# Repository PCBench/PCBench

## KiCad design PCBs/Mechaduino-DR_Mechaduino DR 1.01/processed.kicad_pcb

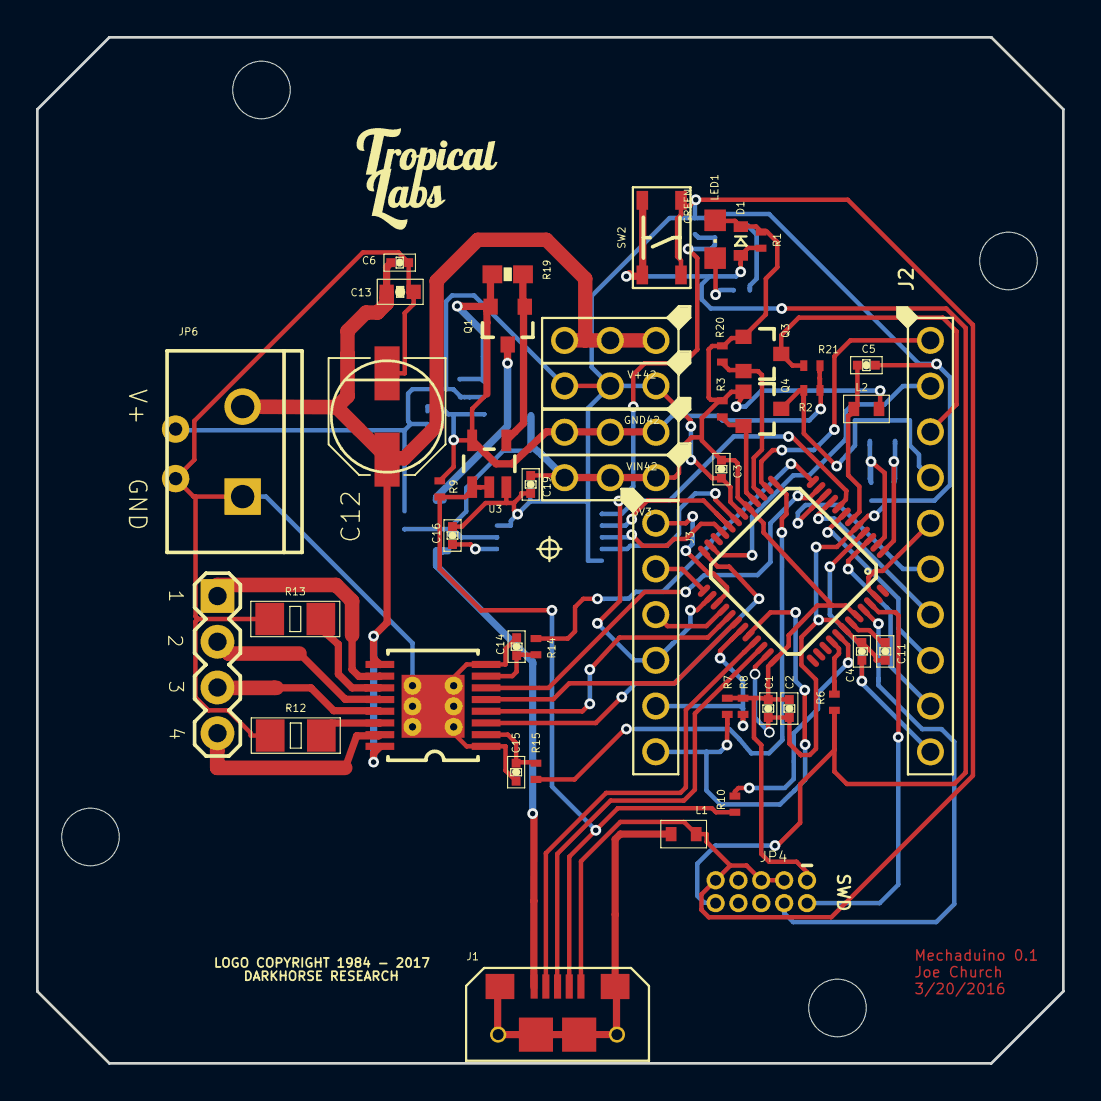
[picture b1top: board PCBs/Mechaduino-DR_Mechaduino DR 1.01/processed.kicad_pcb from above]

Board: 2 copper layers, 57.0 x 57.0 mm, 68 parts (0 on the bottom side), 60 nets.

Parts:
3V3: HEADER_01X03_2.54MM
C1, C2, C3, C4, C5, C9, C14, C15, C16, C19: 0.1uF; SWIFT_0402-CAP
C6: 0.01uF; 0402-CAP
C7, C8: 22pF; SWIFT_0402-CAP
C10: 10uF; 0805-CAP
C11, C17: 1uF; SWIFT_0402-CAP
C12: 100uF; CAPACITORS_ELECTROL_6.6X6.6
C13: 1.0uF; 0603-CAP
C18: 10.0uF; C0805
D1: DIODE_SOD-123
F1: 500mA; FUSE_SMD-PTC-1206
FRAME1: FRAME-LEDGER; CREATIVE_COMMONS
GND42: HEADER_01X03_2.54MM
HS: HS; Heat_Sink
IC1: SAMD21G18A-AUT; TQFP48-7X7
J1: USB_MICRO_RIGHT; USB_MICRO-RIGHT
J2: HEADER_01X10_2.54MM; PTH_2.54MM_01X10
J3: HEADER_01X06_2.54MM
JP4: SWD; CONNECTOR_PINHEAD-2X5-P127
JP6: CONNECTORS_M04PTH
L1: INDUCTOR_0603-TDK
L2: BLM18PG471SN1D; 0603-TDK
LED1: GREEN; CHIPLED_0805
MOTOR_POWER42: SCREWTERMINAL-5MM-2
MOT_GRAPHICS_1: WANTAI_57BYGH115-003B; MOT_GRAPHICS_1
Q1: 2.5A 30V; MOSFET_P_CHANNEL_SOT23
Q2: 2N7002PW; DISCRETE_SEMI_SOT323
Q3, Q4: BSS138; MOSFET-N_CHANNEL_SOT23-3
R1, R9, R16: 100K; R0402
R2, R3, R20, R21: 10K; R0402
R5, R6, R10: 330; R0402
R7, R8: 4.7K; R0402
R12, R13: 0.15 ohm; R1206
R14, R15: 1K; R0402
R19: 47K; 0603-RES
SH1: SHORT-HA5; SHORT_ALL-50
SW2: TACT_4.2MM
U1: AS5047D_TSSOP14
U2: ALLEGRO_A4954_TSSOP16
U3: 74AHC1G125; DIGITAL_IC_SOT23-5
U4: 3.3V_REG; SOT23-5_1
U$3: TROPICAL_LABS_LOGO_1LOGO3; LOGO3
U$5: MECHADUINO_LOGO
V+42: HEADER_01X03_2.54MM
VIN42: HEADER_01X03_2.54MM
Y1: 32,768Khz; CRYSTAL-SMD-2.0X1.2

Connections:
3.3V: 3V3.P$1, 3V3.P$2, 3V3.P$3, C1.1, C2.1, C3.1, C10.1, C17.1, C19.1, D1.K, IC1.17, IC1.36, IC1.44, JP4.1, L2.1, LED1.A, Q3.1, Q4.1, R1.1, R3.1, R7.1, R8.1, R20.1, U1.12, U4.5
/ARDUINO_A0: IC1.3, J2.P$9
/ARDUINO_A1: IC1.7, J2.P$8
/ARDUINO_A2----HEADER_SS: IC1.8, U1.1
/ARDUINO_A3: IC1.9, J2.P$7
/ARDUINO_A4: IC1.10, J2.P$6
/ARDUINO_A5: IC1.47, J2.P$5
/ARDUINO_AREF: C4.1, IC1.4, J2.P$10
/ARDUINO_D0: IC1.16, Q4.2, R3.2
/ARDUINO_D1: IC1.15, Q3.2, R20.2
/ARDUINO_D2: IC1.23, J2.P$2
/ARDUINO_D3: IC1.14, J2.P$1
/ARDUINO_D4----VREF2: IC1.13, R15.2
/ARDUINO_D5----IN3: IC1.24, U2.3
/ARDUINO_D6----IN4: IC1.29, U2.4
/ARDUINO_D7----IN2: IC1.30, U2.5
/ARDUINO_D8----IN1: IC1.11, U2.6
/ARDUINO_D9----VREF1: IC1.12, R14.2
/ARDUINO_D10_SS: IC1.27, J3.P$1
/ARDUINO_D11_MOSI: IC1.25, J3.P$2
/ARDUINO_D12_MISO: IC1.28, J3.P$3
/ARDUINO_D13_SCK: IC1.26, J3.P$4, Q2.1, R16.1
/ARDUINO_D20_SDA: IC1.31, J3.P$5, R8.2
/ARDUINO_D21_SCL: IC1.32, J3.P$6, R7.2
/HEADER_MISO: IC1.21, U1.3
/HEADER_MOSI: IC1.19, U1.4
/HEADER_SCK: IC1.20, U1.2
/HV1: J2.P$3, Q3.3, R21.2
/HV2: J2.P$4, Q4.3, R2.2
/N$1: LED1.C, R5.1
/N$2: R12.2, U2.14
/N$3: Q2.3, R5.2
/N$4: R13.2, U2.11
/N$6: C15.1, R15.1, U2.2
/N$7: J1.4, R9.2, R10.1, U3.1, U3.2
/N$13: JP6.4, U2.15
/N$14: JP6.1, U2.10
/N$15: JP6.2, U2.12
/N$16: JP6.3, U2.13
/N$27: C16.1, U1.11
/N$32: C14.1, R14.1, U2.7
/N$33: F1.2, Q1.3
/N$34: Q1.1, R19.2, U3.4
/N$36: F1.1, J1.1
/PA00_XIN32: C7.2, IC1.1, Y1.2
/PA01_XOUT32: C8.2, IC1.2, Y1.1
/PA28_USB_HOST_EN: IC1.41, R10.2
/PA30_SWCLK: IC1.45, JP4.4
/PA31_SWDIO: IC1.46, JP4.2
/RESET: D1.A, JP4.10, R1.2, R6.1, SW2.P$1, SW2.P$2
/TARGET_RESET_EDBG: IC1.40, R6.2
/TARGET_USB_N: IC1.33, J1.2
/TARGET_USB_P: IC1.34, J1.3
/VDDANA: C5.1, IC1.6, L2.2
/VDDCORE: C11.1, IC1.43
GND: C1.2, C2.2, C3.2, C4.2, C5.2, C7.1, C8.1, C9.2, C10.2, C11.2, C16.2, C17.2, C18.2, C19.2, GND42.P$1, GND42.P$2, GND42.P$3, IC1.5, IC1.18, IC1.35, IC1.42, J1.5, JP4.3, JP4.5, JP4.9, L1.2, Q2.2, R16.2, SH1.2, SW2.P$3, SW2.P$4, U1.5, U1.13, U3.3, U4.2
GND2: C6.2, C12.-, C13.2, C14.2, C15.2, HS.HS, HS.~, MOTOR_POWER42.1, R12.1, R13.1, SH1.1, U2.1, U2.8
SLD: J1.S1, J1.S2, J1.S3, J1.S4, J1.S5, J1.S6, L1.1
V+: C6.1, C12.+, C13.1, MOTOR_POWER42.2, U2.9, U2.16, V+42.P$1, V+42.P$2, V+42.P$3
VIN: C9.1, C18.1, Q1.2, R2.1, R9.1, R19.1, R21.1, U3.5, U4.1, U4.3, VIN42.P$1, VIN42.P$2, VIN42.P$3

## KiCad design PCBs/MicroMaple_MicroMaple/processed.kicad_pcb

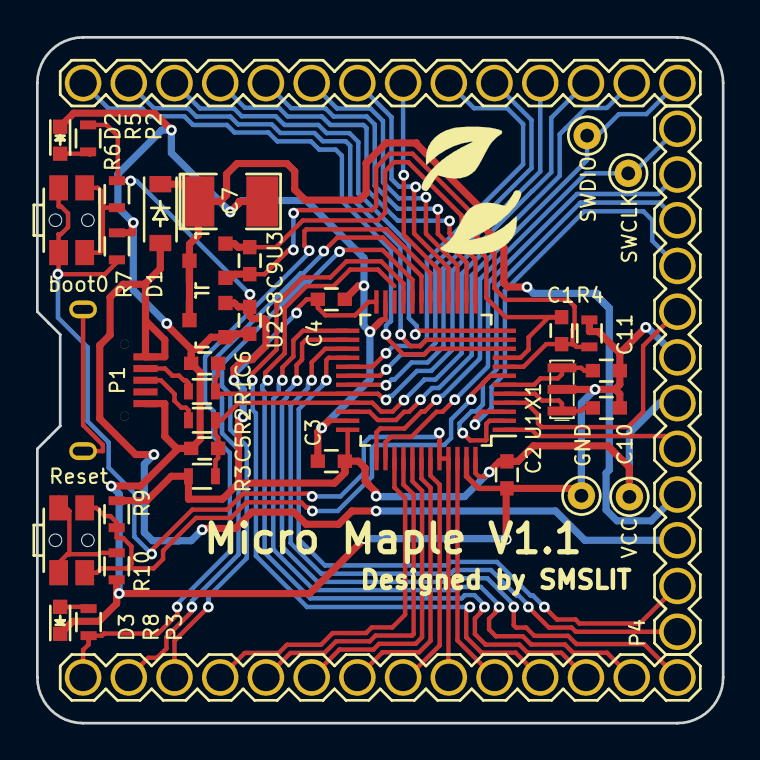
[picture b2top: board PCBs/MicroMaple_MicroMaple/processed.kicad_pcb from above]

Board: 2 copper layers, 38.1 x 38.1 mm, 38 parts (0 on the bottom side), 51 nets.

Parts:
C1, C2, C3, C4: 1uF; C_0603
C5, C6: 47pF; C_0603
C7: 100uF; SMD-1210_Pol
C8, C9: 10uF; C_0603
C10, C11: 18pF; C_0603
D1: D_Small; SOD-123
D2: PWR; LED_0603
D3: GREEN; LED_0603
P1: USB_OTG; USB_Micro-B-MK5
P2, P3: CONN_01X14; Connector_FAD_14x1
P4: CONN_01X12; Connector_FAD_12x1
P5, P6, P7, P8: CONN_01X01; Debug_Pin_1
R1, R2: 22; R_0603
R3: 1.5K; R_0603
R4: 0; R_0603
R5, R6, R8, R10: 1K; R_0603
R7, R9: 10K; R_0603
SW1: USR_BUT; SW_SPST_EVQP7C
SW2: RST_BUTTON; SW_SPST_EVQP7C
U1: STM32F103C8T6; LQFP-48_7x7mm_Pitch0.5mm
U2, U3: XC6206P332MR; SOT-23
X1: 8MHz_OSC; Resonator_3.2x1.5mm

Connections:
+5V: D1.2, P1.1, P4.10
+BATT: C7.1, D1.1, P4.9, U2.3, U3.3
/OSC_IN: C10.2, U1.5, X1.1
/OSC_OUT: C11.2, U1.6, X1.2
/PA0: P2.1, U1.10
/PA1: P2.2, U1.11
/PA2: P2.3, U1.12
/PA3: P2.4, U1.13
/PA4: P2.5, U1.14
/PA5: P2.6, U1.15
/PA6: P2.7, U1.16
/PA7: P2.8, U1.17
/PA8: P2.9, U1.29
/PA9: P2.10, U1.30
/PA10: P2.11, U1.31
/PA11: C6.1, P2.12, R1.1, U1.32
/PA12: C5.1, P2.13, R2.1, R3.1, U1.33
/PA13: P2.14, P5.1, U1.34
/PA14: P4.1, P6.1, U1.37
/PA15: P4.2, U1.38
/PB0: P3.1, R8.2, U1.18
/PB1: P3.2, U1.19
/PB2: P3.3, U1.20
/PB3: P3.4, U1.39
/PB4: P3.5, U1.40
/PB5: P3.6, U1.41
/PB6: P3.7, U1.42
/PB7: P3.8, U1.43
/PB8: P3.9, R7.2, SW1.2, U1.44, U1.45
/PB9: P3.10, U1.46
/PB10: P3.11, U1.21
/PB11: P3.12, U1.22
/PB12: P3.13, U1.25
/PB13: P3.14, U1.26
/PB14: P4.12, U1.27
/PB15: P4.11, U1.28
/PC13: P4.3, U1.2
/PC14: P4.4, U1.3
/PC15: P4.5, U1.4
/RST: R9.1, SW2.1, U1.7
/VBAT: P4.8, U1.1
GND: C2.2, C3.2, C4.2, C5.2, C6.2, C7.2, C8.2, C10.1, C11.1, D2.1, D3.1, P1.5, P4.6, P8.1, R4.1, R7.1, R10.2, U1.23, U1.35, U1.47, U2.1, X1.3
GNDA: C1.1, C9.2, R4.2, U1.8, U3.1
unnamed: D2.2, R5.1
unnamed: D3.2, R8.1
unnamed: P1.2, R1.2
unnamed: P1.3, R2.2
unnamed: R6.2, SW1.1
unnamed: R10.1, SW2.2
VCC: C2.1, C3.1, C4.1, C8.1, P4.7, P7.1, R3.2, R5.2, R6.1, R9.2, U1.24, U1.36, U1.48, U2.2
VDDA: C1.2, C9.1, U1.9, U3.2

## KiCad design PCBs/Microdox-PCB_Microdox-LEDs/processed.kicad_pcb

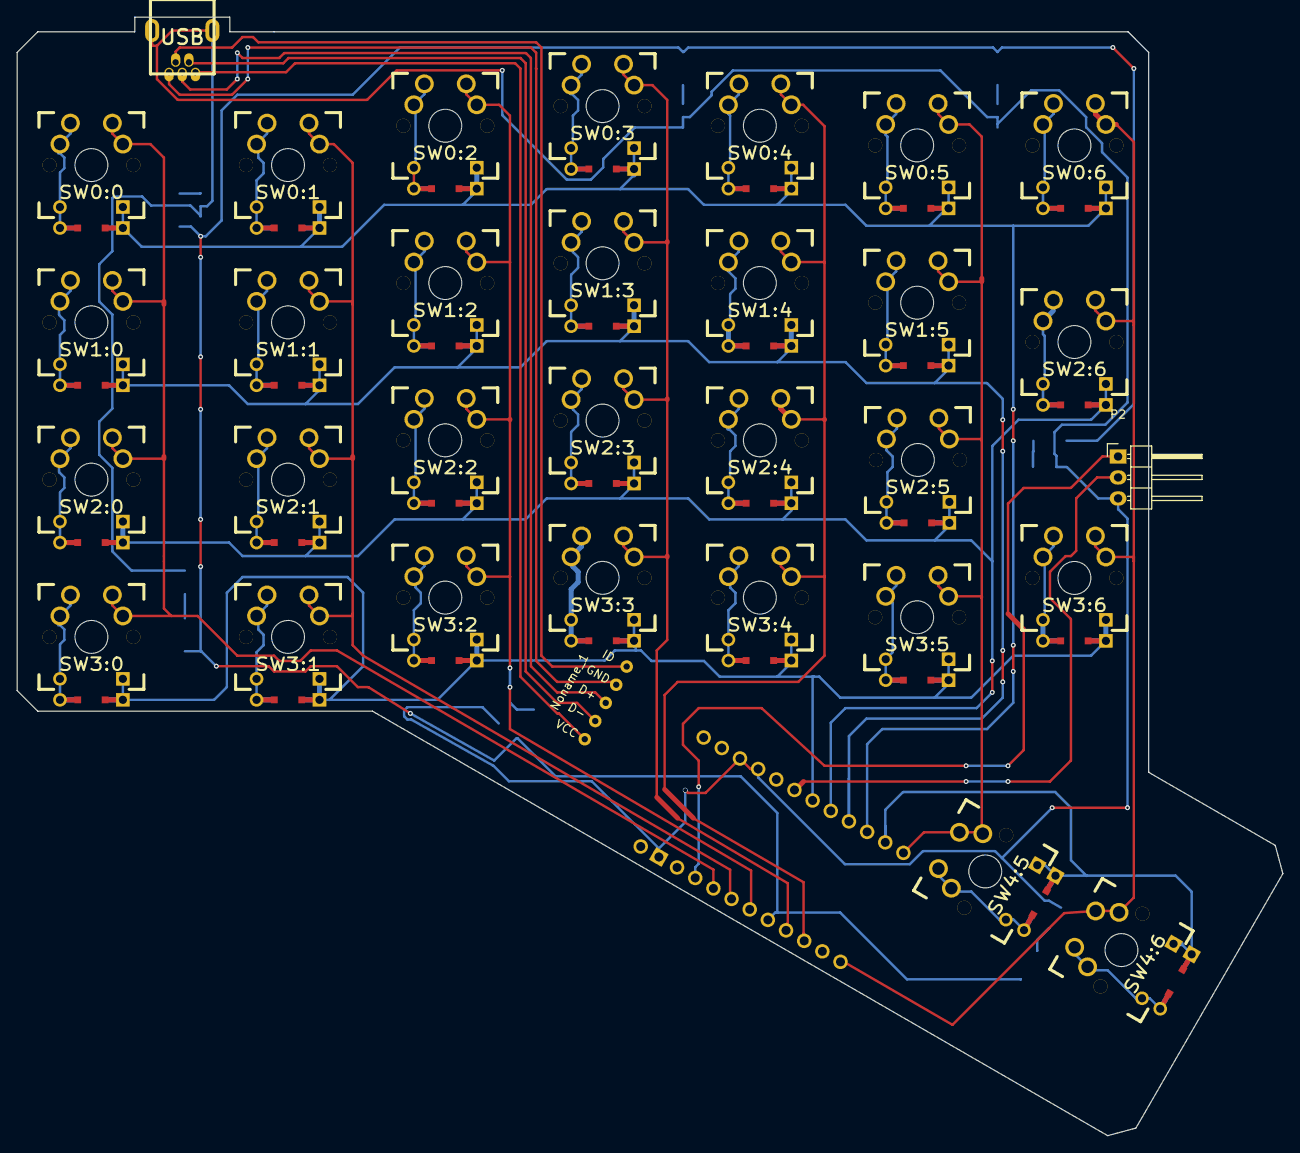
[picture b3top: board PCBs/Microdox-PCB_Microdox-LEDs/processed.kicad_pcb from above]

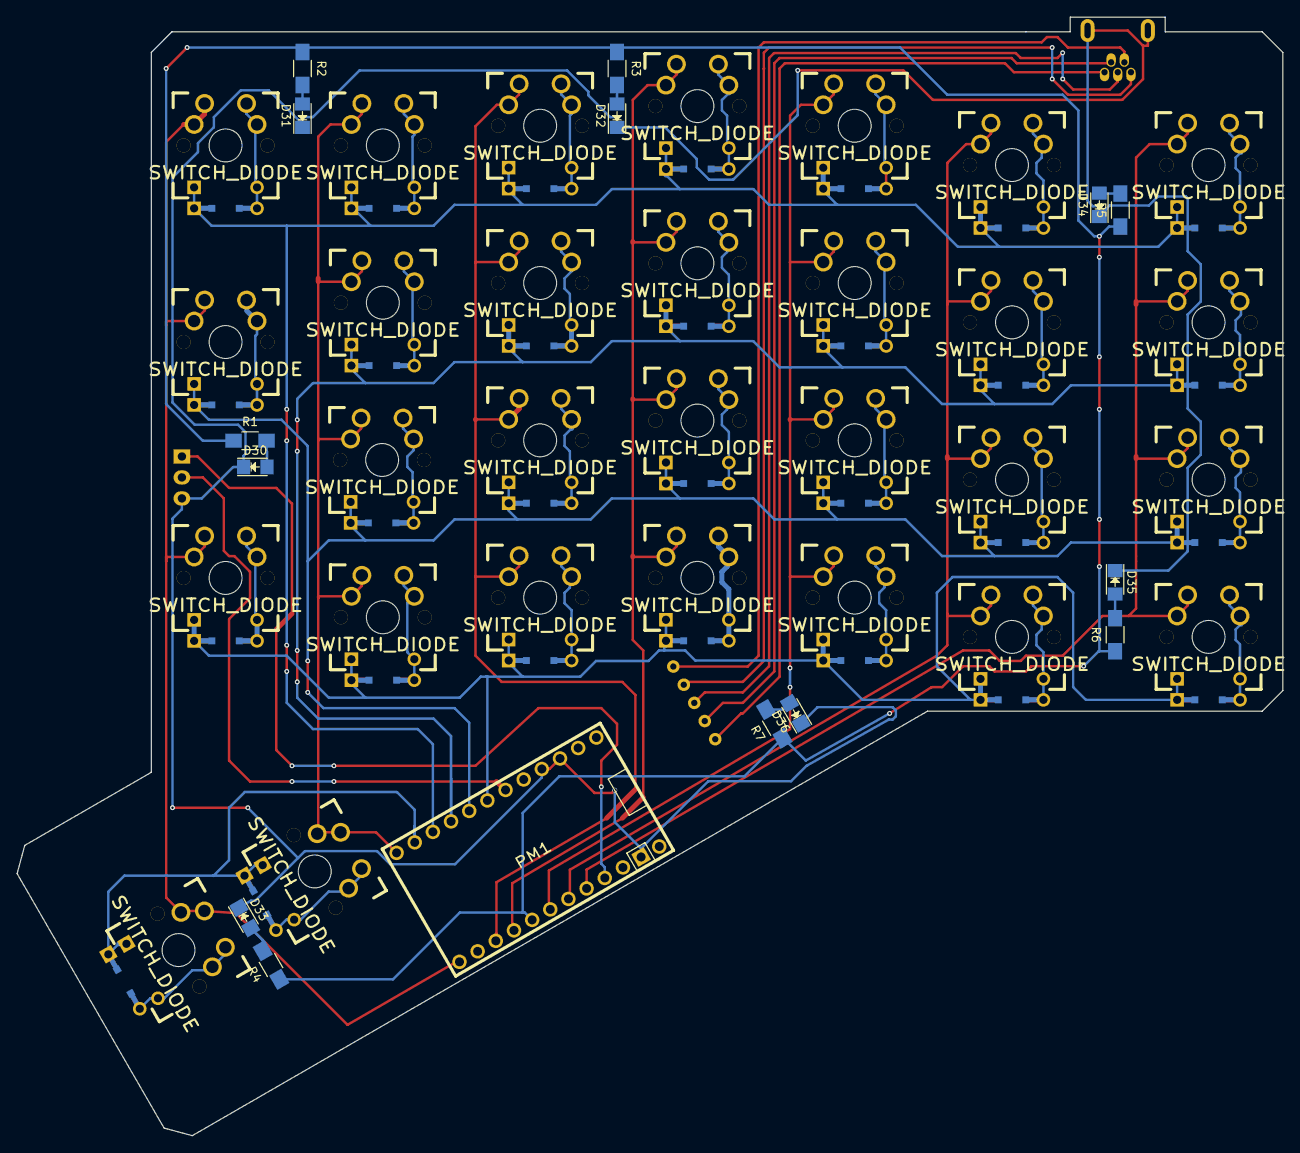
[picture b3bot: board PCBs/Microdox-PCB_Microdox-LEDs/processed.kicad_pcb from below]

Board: 2 copper layers, 153.3 x 135.5 mm, 47 parts (15 on the bottom side), 57 nets.

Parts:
D30, D31, D32, D33, D34, D35, D36: LED; LED_1206
Noname_1: USBWirePins
P1: USB; USBMINI
P2: CONN_01X03; Pin_Header_Angled_1x03
PM1: PROMICRO
R1, R2, R3, R4, R5, R6, R7: 100R; R_1206_HandSoldering
SW0:0, SW0:1, SW0:2, SW0:3, SW0:4, SW0:5, SW0:6, SW1:0, SW1:1, SW1:2, SW1:3, SW1:4, SW1:5, SW2:0, SW2:1, SW2:2, SW2:3, SW2:4, SW2:5, SW2:6, SW3:0, SW3:1, SW3:2, SW3:3, SW3:4, SW3:5, SW3:6, SW4:5, SW4:6: SWITCH_DIODE; MX_FLIP_DIODE

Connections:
/COL0: PM1.16, SW0:0.1, SW1:0.1, SW2:0.1, SW3:0.1
/COL1: PM1.17, SW0:1.1, SW1:1.1, SW2:1.1, SW3:1.1
/COL2: PM1.18, SW0:2.1, SW1:2.1, SW2:2.1, SW3:2.1
/COL3: PM1.20, SW0:3.1, SW1:3.1, SW2:3.1, SW3:3.1
/COL4: PM1.21, SW0:4.1, SW1:4.1, SW2:4.1, SW3:4.1
/COL5: PM1.11, SW0:5.1, SW1:5.1, SW2:5.1, SW3:5.1, SW4:5.1
/COL6: PM1.23, SW0:6.1, SW2:6.1, SW3:6.1, SW4:6.1
/LED+: PM1.19, R1.1, R2.1, R3.1, R4.1, R5.1, R6.1, R7.1
/ROW0: PM1.9, SW0:0.4, SW0:1.4, SW0:2.4, SW0:3.4, SW0:4.4, SW0:5.4, SW0:6.4
/ROW1: PM1.8, SW1:0.4, SW1:1.4, SW1:2.4, SW1:3.4, SW1:4.4, SW1:5.4
/ROW2: PM1.7, SW2:0.4, SW2:1.4, SW2:2.4, SW2:3.4, SW2:4.4, SW2:5.4, SW2:6.4
/ROW3: PM1.6, SW3:0.4, SW3:1.4, SW3:2.4, SW3:3.4, SW3:4.4, SW3:5.4, SW3:6.4
/ROW4: PM1.10, SW4:5.4, SW4:6.4
/SER: P2.2, PM1.5
GND: D30.1, D31.1, D32.1, D33.1, D34.1, D35.1, D36.1, P1.6, P2.3, PM1.2, PM1.3, PM1.13
unnamed: D30.2, R1.2
unnamed: D31.2, R2.2
unnamed: D32.2, R3.2
unnamed: D33.2, R4.2
unnamed: D34.2, R5.2
unnamed: D35.2, R6.2
unnamed: D36.2, R7.2
unnamed: Noname_1.1, P1.1
unnamed: Noname_1.2, P1.2
unnamed: Noname_1.3, P1.3
unnamed: Noname_1.4, P1.4
unnamed: Noname_1.5, P1.5
unnamed: SW0:0.2, SW0:0.3
unnamed: SW0:1.2, SW0:1.3
unnamed: SW0:2.2, SW0:2.3
unnamed: SW0:3.2, SW0:3.3
unnamed: SW0:4.2, SW0:4.3
unnamed: SW0:5.2, SW0:5.3
unnamed: SW0:6.2, SW0:6.3
unnamed: SW1:0.2, SW1:0.3
unnamed: SW1:1.2, SW1:1.3
unnamed: SW1:2.2, SW1:2.3
unnamed: SW1:3.2, SW1:3.3
unnamed: SW1:4.2, SW1:4.3
unnamed: SW1:5.2, SW1:5.3
unnamed: SW2:0.2, SW2:0.3
unnamed: SW2:1.2, SW2:1.3
unnamed: SW2:2.2, SW2:2.3
unnamed: SW2:3.2, SW2:3.3
unnamed: SW2:4.2, SW2:4.3
unnamed: SW2:5.2, SW2:5.3
unnamed: SW2:6.2, SW2:6.3
unnamed: SW3:0.2, SW3:0.3
unnamed: SW3:1.2, SW3:1.3
unnamed: SW3:2.2, SW3:2.3
unnamed: SW3:3.2, SW3:3.3
unnamed: SW3:4.2, SW3:4.3
unnamed: SW3:5.2, SW3:5.3
unnamed: SW3:6.2, SW3:6.3
unnamed: SW4:5.2, SW4:5.3
unnamed: SW4:6.2, SW4:6.3
VCC: P2.1, PM1.15

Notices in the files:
parts and their libraries:
Released under the Creative Commons Attribution Share-Alike 4.0 License
https://creativecommons.org/licenses/by-sa/4.0
